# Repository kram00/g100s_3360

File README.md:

# g100s_3360

original code from https://gist.github.com/qsxcv/53c52e2bf6ed1f0b6c2a8a0d21219476 and https://www.overclock.net/threads/reverse-engineering-3366.1561041/post-28068670

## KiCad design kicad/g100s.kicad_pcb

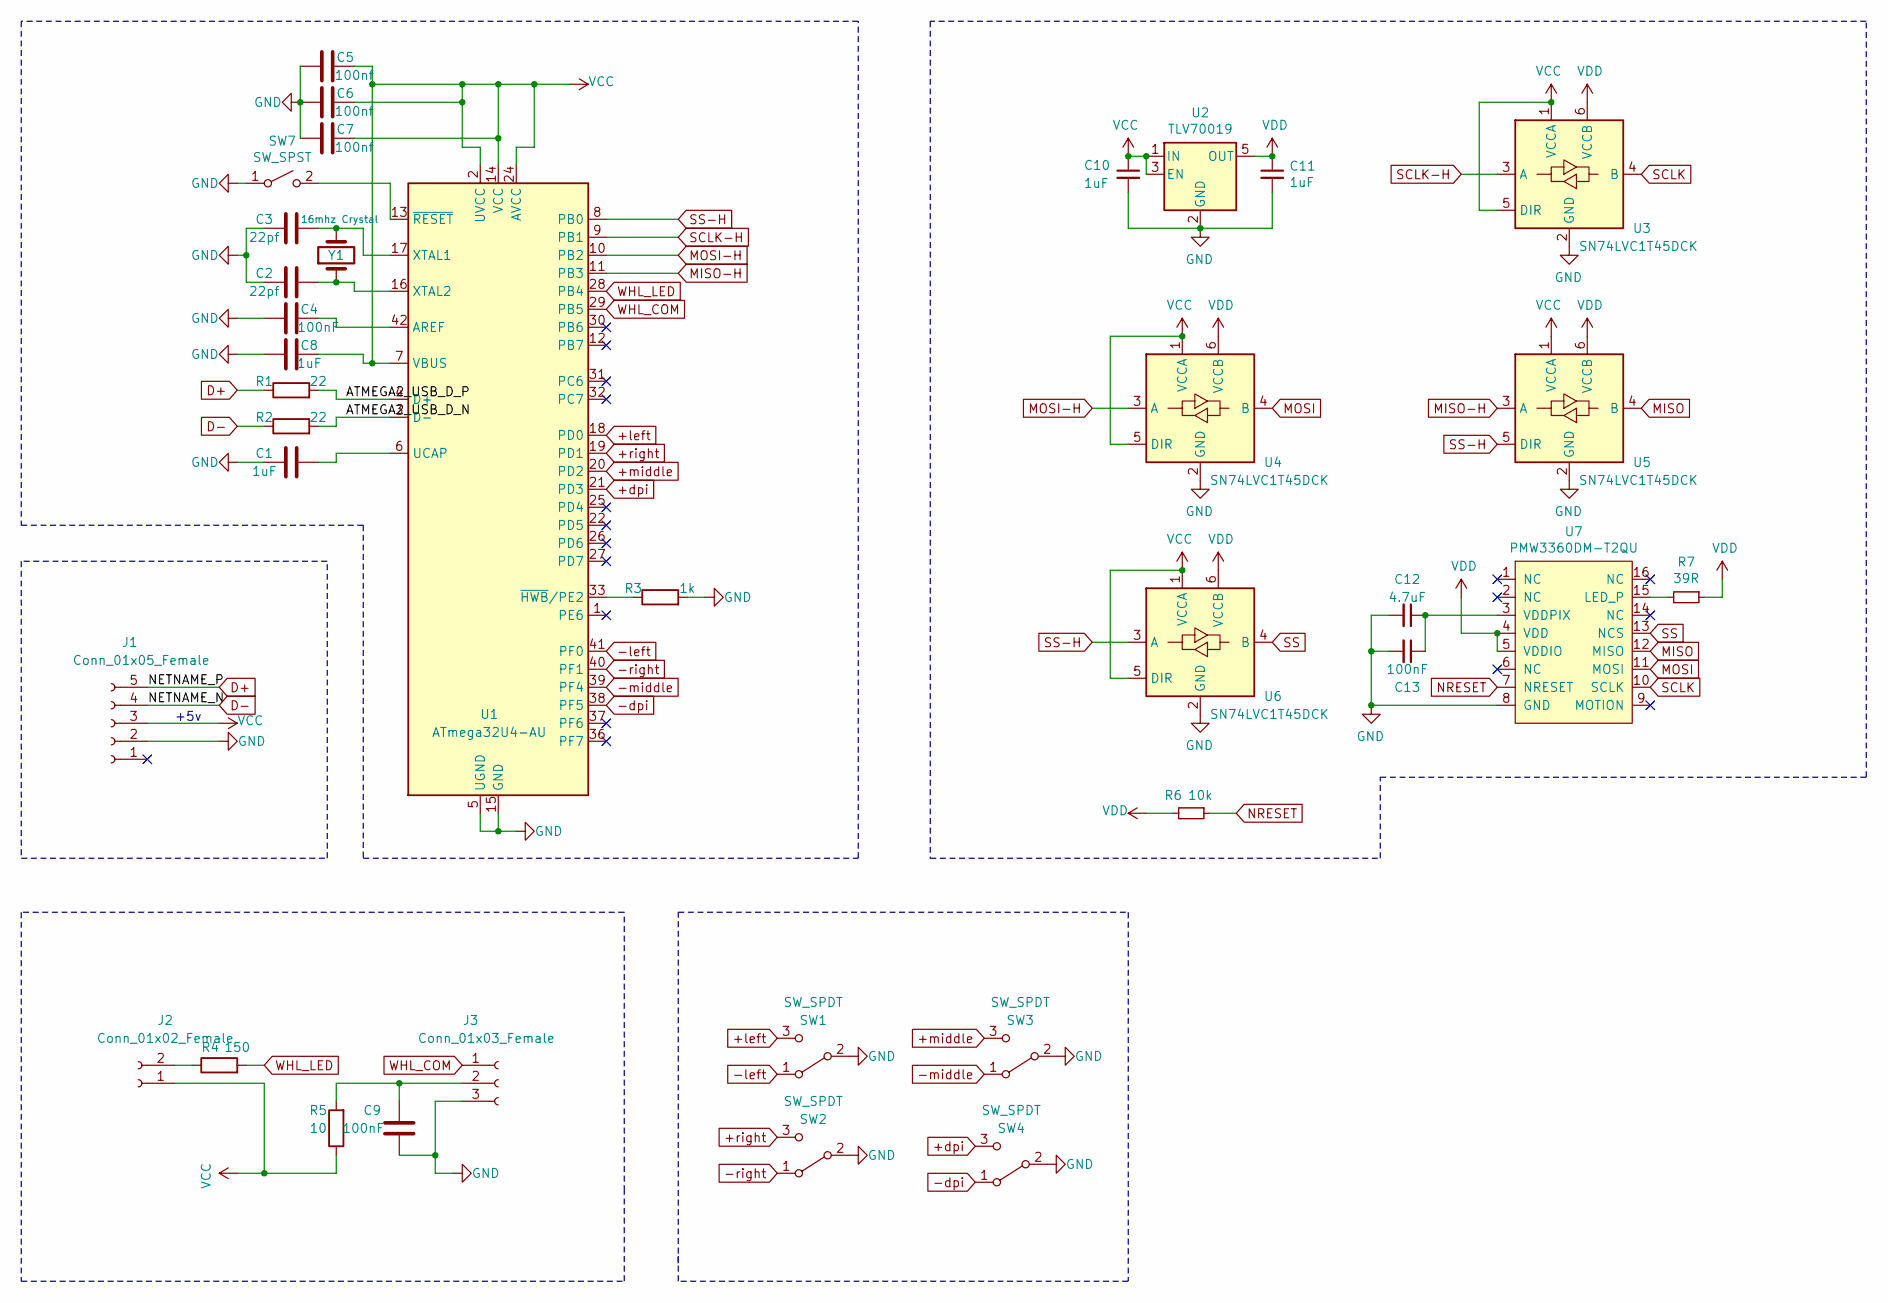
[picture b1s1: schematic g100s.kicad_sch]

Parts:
C1, C8, C10, C11: 1uF; C_0805_2012Metric_Pad1.18x1.45mm_HandSolder
C2, C3: 22pf; C_0805_2012Metric_Pad1.18x1.45mm_HandSolder
C4, C9, C13: 100nF; C_0805_2012Metric_Pad1.18x1.45mm_HandSolder
C5, C6, C7: 100nf; C_0805_2012Metric_Pad1.18x1.45mm_HandSolder
C12: 4.7uF; C_0805_2012Metric_Pad1.18x1.45mm_HandSolder
J1: Conn_01x05_Female; JST_PH_B5B-PH-K_1x05_P2.00mm_Vertical
J2: Conn_01x02_Female; PinSocket_1x02_P2.54mm_Vertical
J3: Conn_01x03_Female; PinSocket_1x03_P2.54mm_Vertical
R1, R2: 22; R_0805_2012Metric_Pad1.20x1.40mm_HandSolder
R3: 1k; R_0805_2012Metric_Pad1.20x1.40mm_HandSolder
R4: 150; R_0805_2012Metric_Pad1.20x1.40mm_HandSolder
R5: 10; R_0805_2012Metric_Pad1.20x1.40mm_HandSolder
R6: 10k; C_0805_2012Metric_Pad1.18x1.45mm_HandSolder
R7: 39R; C_0805_2012Metric_Pad1.18x1.45mm_HandSolder
SW1, SW2, SW3, SW4: SW_SPDT; Microswitch_SPDT_D2F
SW7: SW_SPST; SW_SPST_TL3342
U1: ATmega32U4-AU; TQFP-44_10x10mm_P0.8mm
U2: TLV70019; SOT-23-5
U3, U4, U5, U6: SN74LVC1T45DCK; SOT-363_SC-70-6
U7: PMW3360DM-T2QU
Y1: 16mhz Crystal; Crystal_HC49-U_Vertical

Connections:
+dpi: SW4.3 (C), U1.21 (PD3)
+left: SW1.3 (C), U1.18 (PD0)
+middle: SW3.3 (C), U1.20 (PD2)
+right: SW2.3 (C), U1.19 (PD1)
-dpi: SW4.1 (A), U1.38 (PF5)
-left: SW1.1 (A), U1.41 (PF0)
-middle: SW3.1 (A), U1.39 (PF4)
-right: SW2.1 (A), U1.40 (PF1)
/ATMEGA2_USB_D_N: R2.2, U1.3 (D-)
/ATMEGA2_USB_D_P: R1.2, U1.4 (D+)
D+: J1.5, R1.1
D-: J1.4, R2.1
GND: C1.1, C2.1, C3.1, C4.1, C5.1, C6.2, C7.2, C8.2, C9.1, C10.2, C11.2, C12.2, C13.2, J1.2, J3.3, R3.2, SW1.2 (B), SW2.2 (B), SW3.2 (B), SW4.2 (B), SW7.1 (A), U1.5 (UGND), U1.15 (GND), U1.23 (GND), U1.35 (GND), U1.43 (GND), U2.2 (GND), U3.2 (GND), U4.2 (GND), U5.2 (GND), U6.2 (GND), U7.8 (GND)
MISO: U5.4 (B), U7.12 (MISO)
MISO-H: U1.11 (PB3), U5.3 (A)
MOSI: U4.4 (B), U7.11 (MOSI)
MOSI-H: U1.10 (PB2), U4.3 (A)
NRESET: R6.1, U7.7 (NRESET)
unnamed: C1.2, U1.6 (UCAP)
unnamed: C2.2, U1.16 (XTAL2), Y1.1
unnamed: C3.2, U1.17 (XTAL1), Y1.2
unnamed: C4.2, U1.42 (AREF)
unnamed: C9.2, J3.2, R5.2
unnamed: C12.1, C13.1, U7.3 (VDDPIX)
unnamed: J2.2, R4.1
unnamed: R3.1, U1.33 (~HWB~/PE2)
unnamed: R7.2, U7.15 (LED_P)
unnamed: SW7.2 (B), U1.13 (~RESET)
SCLK: U3.4 (B), U7.10 (SCLK)
SCLK-H: U1.9 (PB1), U3.3 (A)
SS: U6.4 (B), U7.13 (NCS)
SS-H: U1.8 (PB0), U5.5 (DIR), U6.3 (A)
VCC: C5.2, C6.1, C7.1, C8.1, C10.1, J1.3, J2.1, R5.1, U1.2 (UVCC), U1.7 (VBUS), U1.14 (VCC), U1.24 (AVCC), U1.34 (VCC), U1.44 (AVCC), U2.1 (IN), U2.3 (EN), U3.1 (VCCA), U3.5 (DIR), U4.1 (VCCA), U4.5 (DIR), U5.1 (VCCA), U6.1 (VCCA), U6.5 (DIR)
VDD: C11.1, R6.2, R7.1, U2.5 (OUT), U3.6 (VCCB), U4.6 (VCCB), U5.6 (VCCB), U6.6 (VCCB), U7.4 (VDD), U7.5 (VDDIO)
WHL_COM: J3.1, U1.29 (PB5)
WHL_LED: R4.2, U1.28 (PB4)
no_connect_(J1-Pad1): J1.1
no_connect_(U1-Pad1): U1.1 (PE6)
no_connect_(U1-Pad12): U1.12 (PB7)
no_connect_(U1-Pad22): U1.22 (PD5)
no_connect_(U1-Pad25): U1.25 (PD4)
no_connect_(U1-Pad26): U1.26 (PD6)
no_connect_(U1-Pad27): U1.27 (PD7)
no_connect_(U1-Pad30): U1.30 (PB6)
no_connect_(U1-Pad31): U1.31 (PC6)
no_connect_(U1-Pad32): U1.32 (PC7)
no_connect_(U1-Pad36): U1.36 (PF7)
no_connect_(U1-Pad37): U1.37 (PF6)
no_connect_(U2-Pad4): U2.4 (NC)
no_connect_(U7-Pad1): U7.1 (NC)
no_connect_(U7-Pad2): U7.2 (NC)
no_connect_(U7-Pad6): U7.6 (NC)
no_connect_(U7-Pad9): U7.9 (MOTION)
no_connect_(U7-Pad14): U7.14 (NC)
no_connect_(U7-Pad16): U7.16 (NC)

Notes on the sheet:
+5v

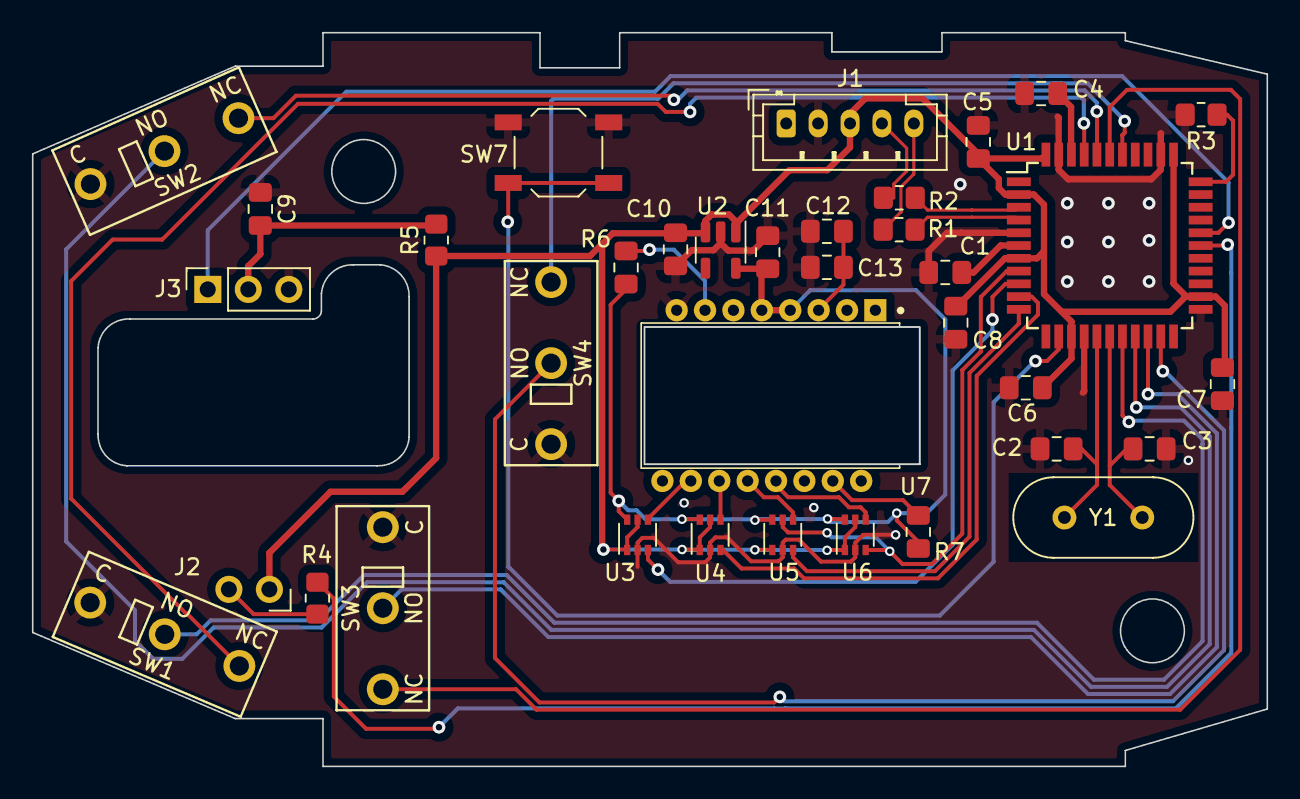
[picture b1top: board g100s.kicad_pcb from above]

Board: 2 copper layers, 77.4 x 46.0 mm, 36 parts (0 on the bottom side), 36 nets.

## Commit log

2021-03-30 save dpi changes to eeprom
2021-04-01 add files
2021-04-03 add delay
2021-04-17 change pmw3360 init
2021-05-10 Remove files
2021-05-10 add hardware debouncing for left and right click
2021-05-28 change OCR0A
2021-06-12 made a custom pcb
2021-06-21 update stl
2021-07-14 update kicad files
2022-07-11 remove sidebuttons
